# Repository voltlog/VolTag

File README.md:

# VolTag
VolTag is an FT232R based breakout board that enhances the FTDI MPSSE (Multi-Protocol Synchronous Serial Engine) to provide the user with a USB to JTAG (SPI, I2C, bit-bang) interface which also has a built-in voltage level translator on the JTAG lines for interfacing to devices that run at a different voltage (between 1.5-5V).

revA has an important bug that prevents communication through the voltage level translating IC because of an incorrect direction configuration. The JTAG interface is still functional through the regular 0.1inch header IO connected directly to the FT232H but you loose the ability to do voltage translation. This issue will be address in revB.

More info about this project in [Voltlog #379](https://youtu.be/LoFzdOF0YcY).

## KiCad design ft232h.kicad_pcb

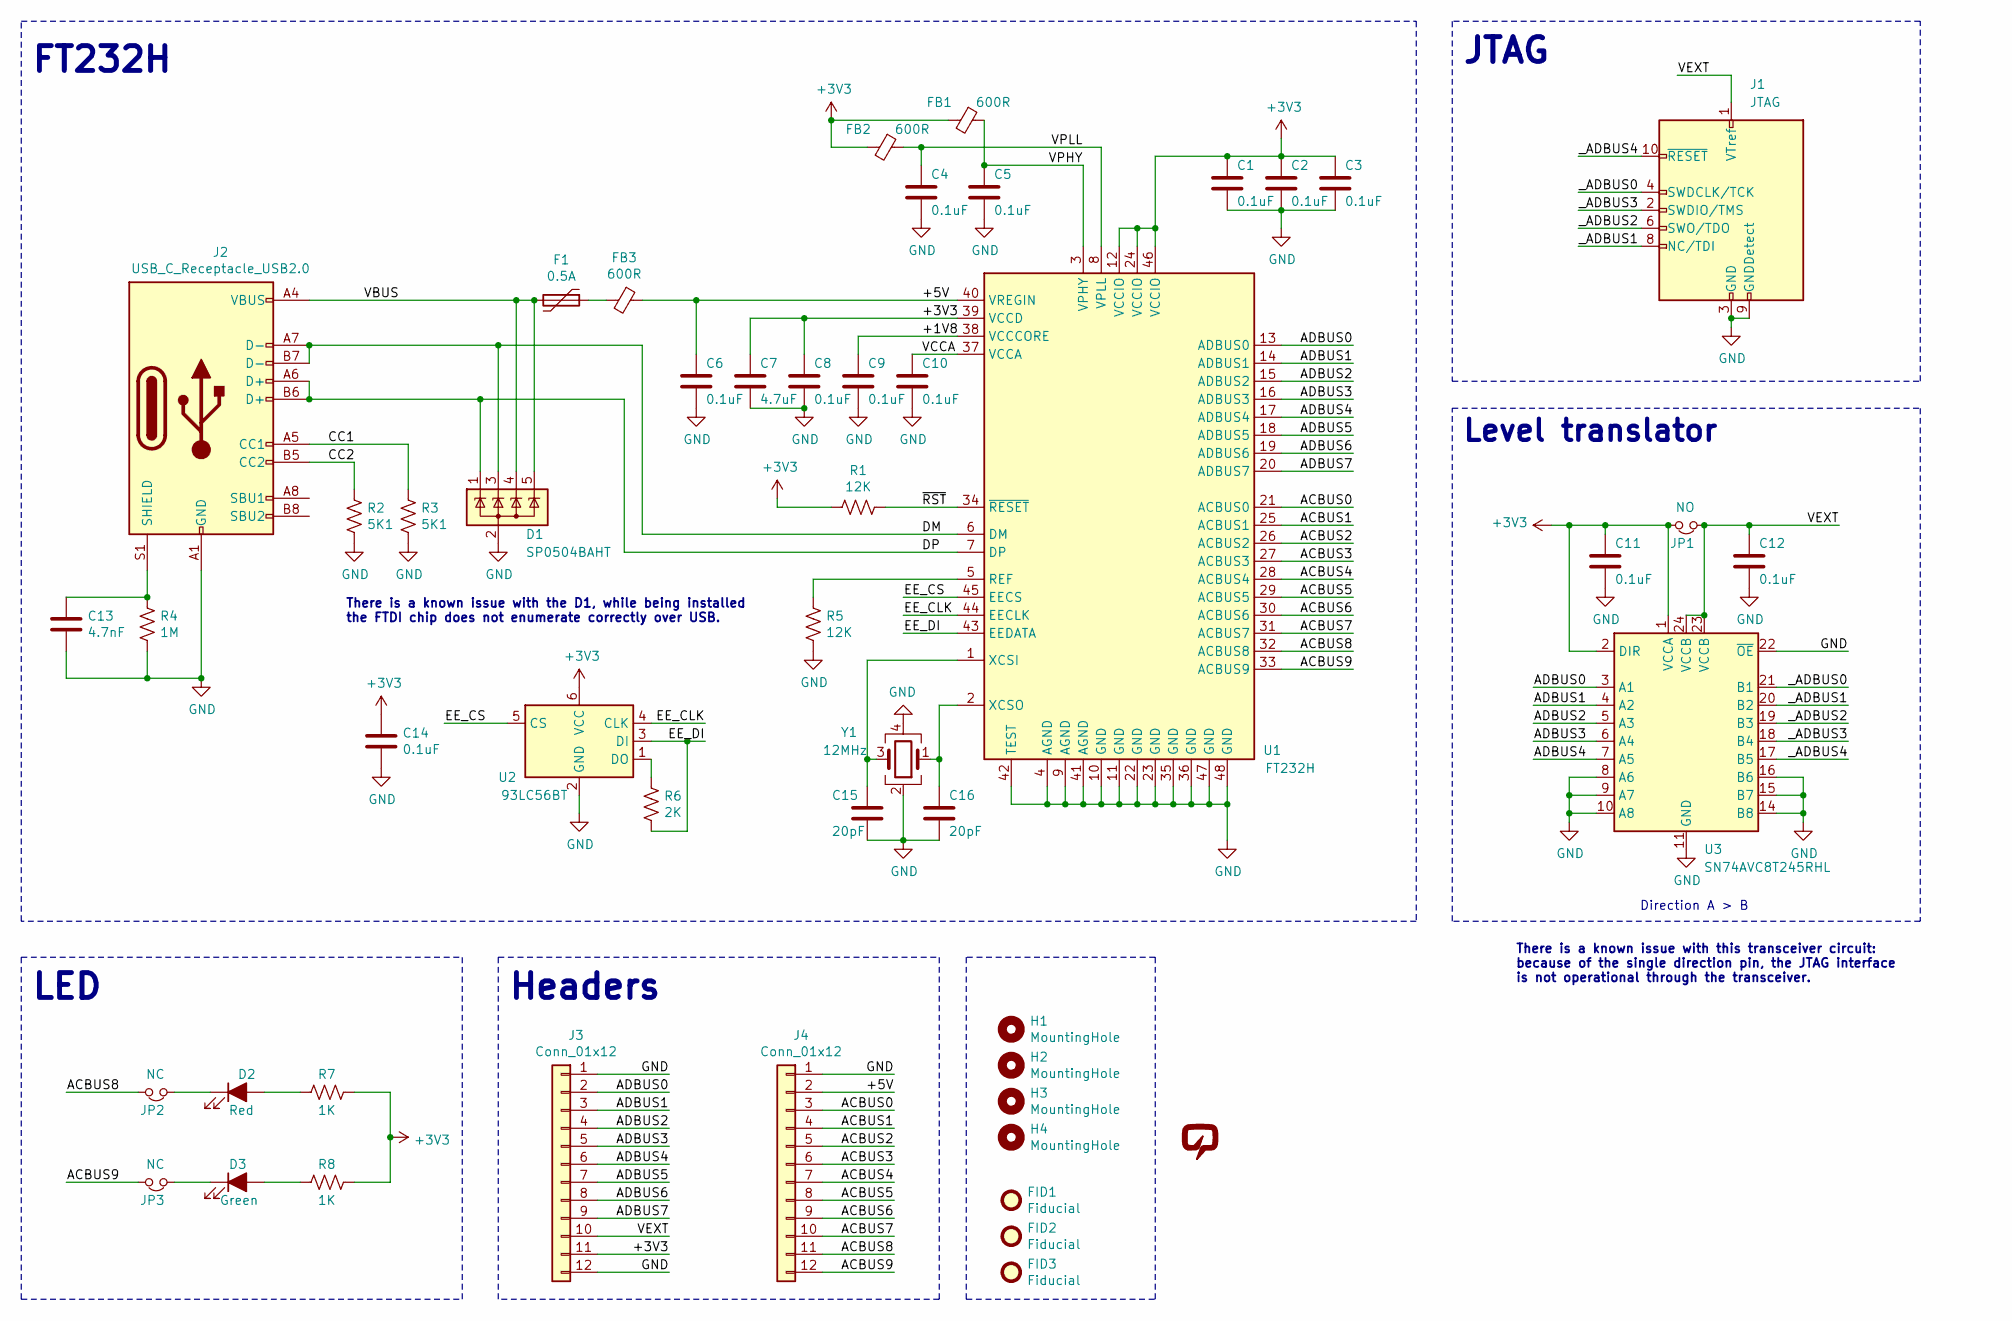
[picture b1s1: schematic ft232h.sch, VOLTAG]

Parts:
C1, C2, C3, C4, C5, C6, C8, C9, C10, C11, C12, C14: 0.1uF; C_0603_1608Metric
C7: 4.7uF; C_0603_1608Metric
C13: 4.7nF; C_1206_3216Metric
C15, C16: 20pF; C_0603_1608Metric
D1: SP0504BAHT; SOT-23-5
D2: Red; LED_0603_1608Metric
D3: Green; LED_0603_1608Metric
F1: 0.5A; Fuse_0603_1608Metric
FB1, FB2, FB3: 600R; L_0603_1608Metric
FID1, FID2, FID3: Fiducial; Fiducial_0.5mm_Mask1mm
H1, H2, H3, H4: MountingHole; MountingHole_3.2mm_M3_DIN965_Pad
J1: JTAG; PinHeader_IDC_2x05_P1.27mm
J2: USB_C_Receptacle_USB2.0; TYPE-C-31-M-12
J3, J4: Conn_01x12; PinHeader_1x12_P2.54mm_Vertical
JP1: NO; PinHeader_1x02_P2.54mm_Vertical
JP2, JP3: NC; SolderJumper-2_P1.3mm_Open_TrianglePad1.0x1.5mm
R1, R5: 12K; R_0603_1608Metric
R2, R3: 5K1; R_0603_1608Metric
R4: 1M; R_1206_3216Metric
R6: 2K; R_0603_1608Metric
R7, R8: 1K; R_0603_1608Metric
U1: FT232H; LQFP-48_7x7mm_P0.5mm
U2: 93LC56BT; SOT-23-6
U3: SN74AVC8T245RHL; Texas_PVQFN-N24
V1: VOLTLOG_LOGO; voltlog_mask_3mm
Y1: 12MHz; Crystal_SMD_3225-4Pin_3.2x2.5mm

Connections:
+3V3: C1.1, C2.1, C3.1, C7.1, C8.1, C11.1, C14.1, FB1.2, FB2.2, J3.11, JP1.2, R1.2, R7.2, R8.2, U1.12 (VCCIO), U1.24 (VCCIO), U1.39 (VCCD), U1.46 (VCCIO), U2.6 (VCC), U3.1 (VCCA), U3.2 (DIR)
/+1V8: C9.1, U1.38 (VCCCORE)
/+5V: C6.1, FB3.1, J4.2, U1.40 (VREGIN)
/ACBUS0: J4.3, U1.21 (ACBUS0)
/ACBUS1: J4.4, U1.25 (ACBUS1)
/ACBUS2: J4.5, U1.26 (ACBUS2)
/ACBUS3: J4.6, U1.27 (ACBUS3)
/ACBUS4: J4.7, U1.28 (ACBUS4)
/ACBUS5: J4.8, U1.29 (ACBUS5)
/ACBUS6: J4.9, U1.30 (ACBUS6)
/ACBUS7: J4.10, U1.31 (ACBUS7)
/ACBUS8: J4.11, JP2.2, U1.32 (ACBUS8)
/ACBUS9: J4.12, JP3.2, U1.33 (ACBUS9)
/ADBUS0: J3.2, U1.13 (ADBUS0), U3.3 (A1)
/ADBUS1: J3.3, U1.14 (ADBUS1), U3.4 (A2)
/ADBUS2: J3.4, U1.15 (ADBUS2), U3.5 (A3)
/ADBUS3: J3.5, U1.16 (ADBUS3), U3.6 (A4)
/ADBUS4: J3.6, U1.17 (ADBUS4), U3.7 (A5)
/ADBUS5: J3.7, U1.18 (ADBUS5)
/ADBUS6: J3.8, U1.19 (ADBUS6)
/ADBUS7: J3.9, U1.20 (ADBUS7)
/CC1: J2.A5 (CC1), R3.1
/CC2: J2.B5 (CC2), R2.1
/DM: D1.3 (K), J2.A7 (D-), J2.B7 (D-), U1.6 (DM)
/DP: D1.1 (K), J2.A6 (D+), J2.B6 (D+), U1.7 (DP)
/EE_CLK: U1.44 (EECLK), U2.4 (CLK)
/EE_CS: U1.45 (EECS), U2.5 (CS)
/EE_DI: R6.2, U1.43 (EEDATA), U2.3 (DI)
/VBUS: D1.4 (K), D1.5 (K), F1.2, J2.A4 (VBUS), J2.A9 (VBUS), J2.B4 (VBUS), J2.B9 (VBUS)
/VCCA: C10.1, U1.37 (VCCA)
/VEXT: C12.1, J1.1 (VTref), J3.10, JP1.1, U3.23 (VCCB), U3.24 (VCCB)
/VPHY: C5.1, FB1.1, U1.3 (VPHY)
/VPLL: C4.1, FB2.1, U1.8 (VPLL)
/_ADBUS0: J1.4 (SWDCLK/TCK), U3.21 (B1)
/_ADBUS1: J1.8 (NC/TDI), U3.20 (B2)
/_ADBUS2: J1.6 (SWO/TDO), U3.19 (B3)
/_ADBUS3: J1.2 (SWDIO/TMS), U3.18 (B4)
/_ADBUS4: J1.10 (~RESET~), U3.17 (B5)
/~RST: R1.1, U1.34 (~RESET)
GND: C1.2, C2.2, C3.2, C4.2, C5.2, C6.2, C7.2, C8.2, C9.2, C10.2, C11.2, C12.2, C13.2, C14.2, C15.2, C16.2, D1.2 (A), J1.3 (GND), J1.5 (GND), J1.9 (GNDDetect), J2.A1 (GND), J2.A12 (GND), J2.B1 (GND), J2.B12 (GND), J3.1, J3.12, J4.1, R2.2, R3.2, R4.2, R5.2, U1.4 (AGND), U1.9 (AGND), U1.10 (GND), U1.11 (GND), U1.22 (GND), U1.23 (GND), U1.35 (GND), U1.36 (GND), U1.41 (AGND), U1.42 (TEST), U1.47 (GND), U1.48 (GND), U2.2 (GND), U3.8 (A6), U3.9 (A7), U3.10 (A8), U3.11 (GND), U3.12 (GND), U3.13 (GND), U3.14 (B8), U3.15 (B7), U3.16 (B6), U3.22 (~OE), U3.25 (GND), Y1.2, Y1.4
unnamed: C13.1, J2.S1 (SHIELD), R4.1
unnamed: C15.1, U1.1 (XCSI), Y1.3
unnamed: C16.1, U1.2 (XCSO), Y1.1
unnamed: D2.1 (K), JP2.1
unnamed: D2.2 (A), R7.1
unnamed: D3.1 (K), JP3.1
unnamed: D3.2 (A), R8.1
unnamed: F1.1, FB3.2
unnamed: R5.1, U1.5 (REF)
unnamed: R6.1, U2.1 (DO)

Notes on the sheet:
FT232H
JTAG
Headers
LED
Level translator
Direction A > B
There is a known issue with this transceiver circuit: because of the single direction pin, the JTAG interface is not operational through the transceiver.
There is a known issue with the D1, while being installed the FTDI chip does not enumerate correctly over USB.

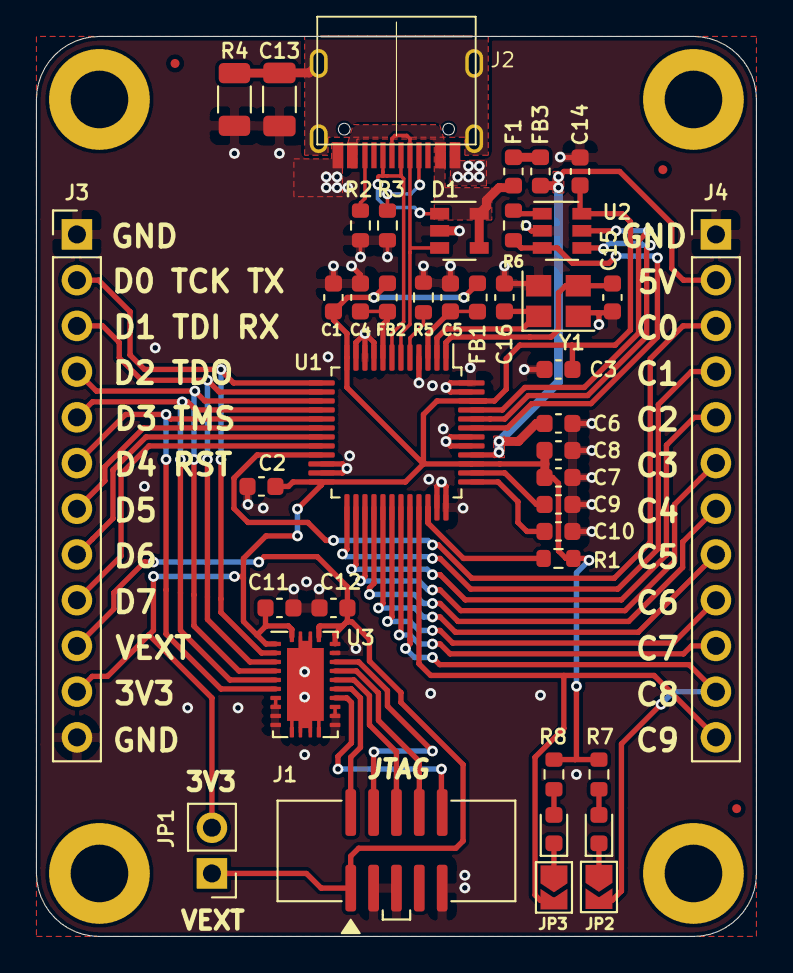
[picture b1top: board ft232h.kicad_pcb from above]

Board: 2 copper layers, 40.0 x 50.0 mm, 50 parts (0 on the bottom side), 50 nets.

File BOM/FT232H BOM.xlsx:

FT232H Bill of Material
Ref | Qnty | Value | Cmp name | Footprint | Description | LCSC # | Digikey #
C1, C2, C3, C4, C5, C6, C8, C9, C10, C11, C12, C14, | 12 | 0.1uF | C | Capacitor_SMD:C_0603_1608Metric | Unpolarized capacitor | C1591
C7, | 1 | 4.7uF | C | Capacitor_SMD:C_0603_1608Metric | Unpolarized capacitor | C19666
C13, | 1 | 4.7nF | C | Capacitor_SMD:C_1206_3216Metric | Unpolarized capacitor | C1621
C15, C16, | 2 | 20pF | C | Capacitor_SMD:C_0603_1608Metric | Unpolarized capacitor | C1648
D1, | 1 | SP0504BAHT | SP0504BAHT | Package_TO_SOT_SMD:SOT-23-5 | TVS Diode Array, 5.5V Standoff, 4 Channels, SOT-23-5 package | C10675
D2, | 1 | Red | LED_ALT | LED_SMD:LED_0603_1608Metric | Light emitting diode, filled shape | C84263
D3, | 1 | Green | LED_ALT | LED_SMD:LED_0603_1608Metric | Light emitting diode, filled shape | C84267
F1, | 1 | 0.5A | Polyfuse | Fuse:Fuse_0603_1608Metric | Resettable fuse, polymeric positive temperature coefficient | C210357
FB1, FB2, FB3, | 3 | 600R | Ferrite_Bead_Small | Inductor_SMD:L_0603_1608Metric | Ferrite bead, small symbol | C107335
J1, | 1 | JTAG | Conn_ARM_JTAG_SWD_10 | voltlog:PinHeader_IDC_2x05_P1.27mm | Cortex Debug Connector, standard ARM Cortex-M SWD and JTAG interface | - | 1175-1629-ND
J2, | 1 | USB_C_Receptacle_USB2.0 | USB_C_Receptacle_USB2.0 | voltlog:TYPE-C-31-M-12 | USB 2.0-only Type-C Receptacle connector | C165948
J3, J4, | 2 | Conn_01x12 | Conn_01x12 | Connector_PinHeader_2.54mm:PinHeader_1x12_P2.54mm_Vertical | Generic connector, single row, 01x12, script generated (kicad-library-utils/sch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 | C225487
JP1, | 1 | NO | Jumper_NC_Small | Connector_PinHeader_2.54mm:PinHeader_1x02_P2.54mm_Vertical | Jumper, normally closed, small symbol | C358684
JP2, JP3, | 2 | NC | Jumper_NC_Small | Jumper:SolderJumper-2_P1.3mm_Open_TrianglePad1.0x1.5mm | Jumper, normally closed, small symbol | DNP
R1, R5, | 2 | 12K | R_US | Resistor_SMD:R_0603_1608Metric | Resistor, US symbol | C22790
R2, R3, | 2 | 5K1 | R_US | Resistor_SMD:R_0603_1608Metric | Resistor, US symbol | C105580
R4, | 1 | 1M | R_US | Resistor_SMD:R_1206_3216Metric | Resistor, US symbol | C105578
R6, | 1 | 2K | R_US | Resistor_SMD:R_0603_1608Metric | Resistor, US symbol | C22975
R7, R8, | 2 | 1K | R_US | Resistor_SMD:R_0603_1608Metric | Resistor, US symbol | C21190
U1, | 1 | FT232H | FT232H | Package_QFP:LQFP-48_7x7mm_P0.5mm | Hi Speed Single Channel USB UART/FIFO, LQFP/QFN-48 (Voltlog symbol) | C51997
U2, | 1 | 93LC56BT | 93LCxxBxxOT | Package_TO_SOT_SMD:SOT-23-6 | Serial EEPROM, 93 Series, 2.5V, SOT-23-6 | C190271
U3, | 1 | SN74AVC8T245RHL | SN74AVC8T245RHL | voltlog:Texas_PVQFN-N24 | 8-Bit Dual-Supply Bus Transceiver With Configurable Voltage Translation and 3-S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 | C105245
Y1, | 1 | 12MHz | Crystal_GND24 | Crystal:Crystal_SMD_3225-4Pin_3.2x2.5mm | Four pin crystal, GND on pins 2 and 4 | C9002

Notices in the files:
ft232h.sch:
License GPLv3
